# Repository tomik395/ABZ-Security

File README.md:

# ABZ Security Box

The ABZ Security Box is a security program created for ESP32-S3. This software is capable of measuring distances using a distance sensor, setting off an alarm if anything comes too close, and sending alerts via SMS. This program is specifically designed to be controlled remotely using SMS commands. The ABZ Security Box is meant to be mounted to a wall where an opening door would intersect the ultrasonic sensor line-of-sight.

This was a final team project at the University of California, San Diego for ECE 196 (Hands-on Engineering Project).

An adjustable DC Boost Converter Workshop is also attached for speaker voltage adjustments. Learn about the LM2577-ADJ IC:
For more details, see [details](ABZ%20Workshop%20LM2577-ADJ.pdf).

Please visit our website at:
https://sites.google.com/view/abz-secure

## Installation and Requirements

- You will need to install the TwilioLib library into your Arduino environment before you can compile and upload the code to your Arduino device.
- You will need a constant and stable WiFi connection to maintain SMS communication.
- This code is compatible with any ESP32 with WiFi capability. Wifi-capable Arduino devices will require code alteration due to differing WiFi connection libraries.

## PCB Design

PCB design and result images are provided on our website for users wishing to design the system from scratch, as opposed to a pre-made ESP32 device. KiCad was used to design the prototype. Since this design uses plenty of small ICs and 0402 footprint passive components, either PCB manufacturer assembly or a reflow oven is required.

If users wish to veer away from a PCB design, this code and the schematics found in the PCB files folder are compatible with any pre-made ESP32 device.

## Variables

- `commandLoopCounter` - Count of the loop iterations to control how frequently we search for new commands.
- `notificationHelp`, `notificationReset`, `notificationStatus`, `notificationLowBatt`, `notificationCritBatt`, `notificationNoBatt` - Boolean flags to track the status of notifications.
- `ssid`, `password` - Your Wifi network's SSID and password.
- `account_sid`, `auth_token`, `from_number`, `to_number` - Your Twilio account SID, Auth Token, sender number, and receiver number.
- `deactivationCode` - The deactivation code to disarm the alarm.
- `mostRecentMessage` - The most recent message sent to the Twilio phone number.
- `armed` - Boolean flag to track if the system is armed.
- `trigPin`, `echoPin`, `MosfetPin` - The pins connected to the ultrasonic sensor and alarm.
- `SOUND_SPEED`, `CM_TO_INCH`, `MAX_ANALOG_VAL`, `MAX_BATTERY_VOLTAGE` - Constants used for distance and battery level calculation.
- `duration`, `distanceInch`, `AverageDistanceInch`, `SafeDistanceInch`, `SafeDistanceInchMinus`, `SafeDistanceInchPositive`, `Safe`, `SafeCount` - Variables used for distance calculation and safety checking.
- `alpha`, `alphaDelta`, `betaDelta`, `SafeWindow`, `SafeCountTrigger` - Variables used for controlling the distance measurement and checking routines.

## SMS Commands

The following commands are available for controlling the ABZ Security System:

- `Help` - The system will reply with a list of available commands.
- `Arm` - The system will arm the alarm and start checking for intrusions.
- `Disarm` - The system will disarm the alarm.
- `Reset` - The system will ask for confirmation, then reset the device.
- `Status` - The system will send back its current status including the current battery level and whether it's armed.

  These commands are sent by replying to the system's messages.

## Key Functions

- `clearNotificationBlocks` - Clear the flags used to track if notifications have been sent.
- `status` - Get the current status of the system as a string.
- `measureAverageDistance` - Measure the average distance over a number of iterations.
- `lowBatteryNotification` - Check the battery level and send notifications if it's too low.
- `measureBattery` - Measure the current battery level.
- `measureDistance` - Measure the distance using the ultrasonic sensor once.
- `setSafeDistance` - Measure and set the safe distance.
- `questionSafety` - Check if a given distance is within the safe range.
- `setAlarmHigh` - Set the alarm to a high state (i.e., turn it on).
- `setAlarmLow` - Set the alarm to a low state (i.e., turn it off).
- `beeper` - Beep the alarm for a certain duration.
- `sendText` - Send an SMS message using Twilio.
- `getConversation` - Get the most recent message from the Twilio phone number.
- `generateMessage` - Generate a break-in alert message.
- `searchDisarmCode` - Check if the most recent message is the disarm code.
- `searchCommands` - Check if the most recent message is one of the command words.
- `alertBreakIn` - Send a break-in alert and start the alarm.
- `setup` - Set up the device. This function is called once when the device is turned on.
- `loop` - The main loop of the device. This function is called repeatedly.

## Battery Monitoring

The system includes battery level monitoring. It sends a text notification when the battery level falls below certain thresholds:

- Below 30%: A warning is sent to charge the battery
- Below 10%: A critical battery warning is sent, indicating that the system will soon shut down
- Battery level reaches 0: The system sends a final notification before shutting down

  These commands are sent by replying to the system's messages.

  The system is charged by plugging in a USB C.

## Contributing

Contributions to the ABZ Security System are welcome. Please create a pull request with your changes or enhancements, ensuring that the code is well-formatted and includes comments where necessary.

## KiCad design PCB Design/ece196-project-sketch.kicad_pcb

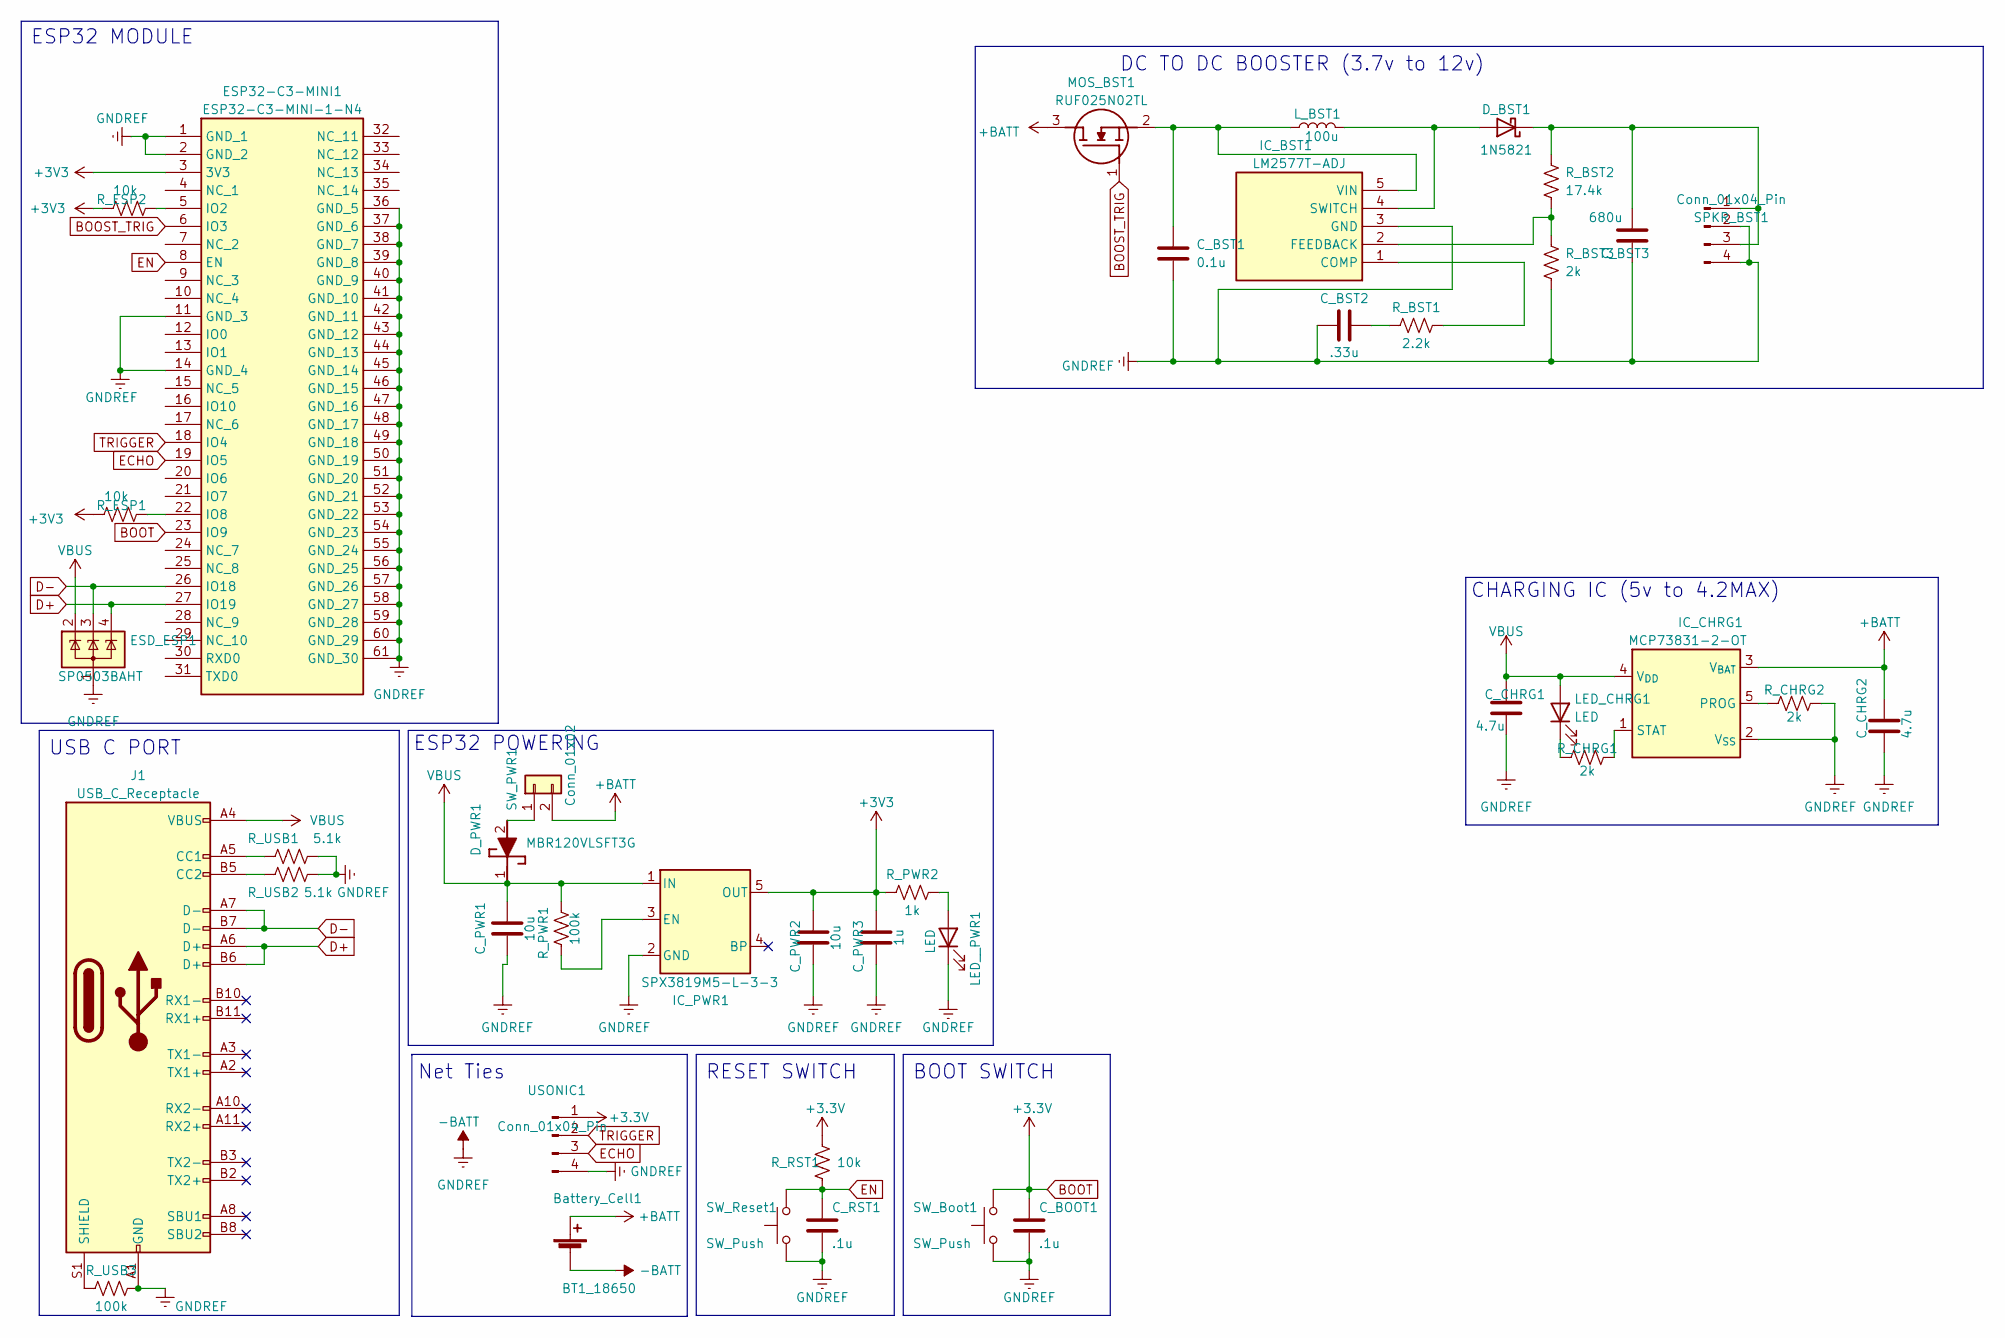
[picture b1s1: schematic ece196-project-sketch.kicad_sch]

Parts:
BT1_18650: Battery_Cell1; BatteryHolder_Keystone_1042_1x18650
C_BOOT1: .1u; C_0402_1005Metric
C_BST1: 0.1u; C_1812_4532Metric
C_BST2: .33u; C_1812_4532Metric
C_BST3: 680u; CP_Radial_D8.0mm_P5.00mm
C_CHRG1, C_CHRG2: 4.7u; C_0402_1005Metric
C_PWR1, C_PWR2: 10u; C_0402_1005Metric
C_PWR3: 1u; C_0402_1005Metric
C_RST1: .1u; C_0402_1005Metric
D_BST1: 1N5821; D_DO-201AD_P15.24mm_Horizontal
D_PWR1: MBR120VLSFT3G; SODFL3616X98N; Manufacturer_Part_Number MBR120VLSFT3G; Mouser Part Number 863-MBR120VLSFT3G
ESD_ESP1: SP0503BAHT; SOT-143
ESP32-C3-MINI1: ESP32-C3-MINI-1-N4; ESP32C3MINI1N4; Manufacturer_Part_Number ESP32-C3-MINI-1-N4; Mouser Part Number 356-ESP32-C3-MINI1N4
IC_BST1: LM2577T-ADJ; TPS75833KC; Manufacturer_Part_Number LM2577T-ADJ; Mouser Part Number 926-LM2577T-ADJ
IC_CHRG1: MCP73831-2-OT; SOT-23-5
IC_PWR1: SPX3819M5-L-3-3; SOT-23-5
J1: USB_C_Receptacle; USB_C_Receptacle_JAE_DX07S016JA1R1500
LED_CHRG1: LED; LED_0805_2012Metric
LED__PWR1: LED; LED_0805_2012Metric
L_BST1: 100u; L_Bourns-SRN1060
MOS_BST1: RUF025N02TL; Mouser Part Number 755-RUF025N02TL
R_BST1: 2.2k; R_2010_5025Metric
R_BST2: 17.4k; R_2010_5025Metric
R_BST3: 2k; R_2010_5025Metric
R_CHRG1, R_CHRG2: 2k; R_0402_1005Metric
R_ESP1, R_ESP2: 10k; R_0402_1005Metric
R_PWR1: 100k; R_0402_1005Metric
R_PWR2: 1k; R_0402_1005Metric
R_RST1: 10k; R_0402_1005Metric
R_USB1, R_USB2: 5.1k; R_0402_1005Metric
R_USB3: 100k; R_0402_1005Metric
SPKR_BST1: Conn_01x04_Pin; JST_PH_B4B-PH-K_1x04_P2.00mm_Vertical
SW_Boot1: SW_Push; SW_SPST_Omron_B3FS-100xP
SW_PWR1: Conn_01x02; PinHeader_1x02_P2.54mm_Vertical
SW_Reset1: SW_Push; SW_SPST_Omron_B3FS-100xP
USONIC1: Conn_01x04_Pin; JST_PH_B4B-PH-K_1x04_P2.00mm_Vertical

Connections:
+3V3: C_PWR2.2, C_PWR3.2, ESP32-C3-MINI1.3 (3V3), IC_PWR1.5 (OUT), R_ESP1.1, R_ESP2.1, R_PWR2.2
+BATT: BT1_18650.1 (+), C_CHRG2.2, IC_CHRG1.3 (V_{BAT}), MOS_BST1.3 (D), SW_PWR1.2
-BATT: BT1_18650.2 (-), C_BOOT1.1, C_BST1.2, C_BST2.1, C_BST3.2, C_CHRG1.1, C_CHRG2.1, C_PWR1.1, C_PWR2.1, C_PWR3.1, C_RST1.1, ESD_ESP1.1 (A), ESP32-C3-MINI1.1 (GND_1), ESP32-C3-MINI1.2 (GND_2), ESP32-C3-MINI1.11 (GND_3), ESP32-C3-MINI1.14 (GND_4), ESP32-C3-MINI1.36 (GND_5), ESP32-C3-MINI1.37 (GND_6), ESP32-C3-MINI1.38 (GND_7), ESP32-C3-MINI1.39 (GND_8), ESP32-C3-MINI1.40 (GND_9), ESP32-C3-MINI1.41 (GND_10), ESP32-C3-MINI1.42 (GND_11), ESP32-C3-MINI1.43 (GND_12), ESP32-C3-MINI1.44 (GND_13), ESP32-C3-MINI1.45 (GND_14), ESP32-C3-MINI1.46 (GND_15), ESP32-C3-MINI1.47 (GND_16), ESP32-C3-MINI1.48 (GND_17), ESP32-C3-MINI1.49 (GND_18), ESP32-C3-MINI1.50 (GND_19), ESP32-C3-MINI1.51 (GND_20), ESP32-C3-MINI1.52 (GND_21), ESP32-C3-MINI1.53 (GND_22), ESP32-C3-MINI1.54 (GND_23), ESP32-C3-MINI1.55 (GND_24), ESP32-C3-MINI1.56 (GND_25), ESP32-C3-MINI1.57 (GND_26), ESP32-C3-MINI1.58 (GND_27), ESP32-C3-MINI1.59 (GND_28), ESP32-C3-MINI1.60 (GND_29), ESP32-C3-MINI1.61 (GND_30), IC_BST1.3 (GND), IC_CHRG1.2 (V_{SS}), IC_PWR1.2 (GND), J1.A1 (GND), J1.A12 (GND), J1.B1 (GND), J1.B12 (GND), LED__PWR1.1 (K), R_BST3.2, R_CHRG2.2, R_USB1.1, R_USB2.1, R_USB3.1, SPKR_BST1.2, SPKR_BST1.4, SW_Boot1.1, SW_Reset1.1, USONIC1.4
BOOST_TRIG: ESP32-C3-MINI1.6 (IO3), MOS_BST1.1 (G)
BOOT: C_BOOT1.2, ESP32-C3-MINI1.23 (IO9), R_RST1.1, SW_Boot1.2, USONIC1.1
D+: ESD_ESP1.4 (K), ESP32-C3-MINI1.27 (IO19), J1.A6 (D+), J1.B6 (D+)
D-: ESD_ESP1.3 (K), ESP32-C3-MINI1.26 (IO18), J1.A7 (D-), J1.B7 (D-)
ECHO: ESP32-C3-MINI1.19 (IO5), USONIC1.3
EN: C_RST1.2, ESP32-C3-MINI1.8 (EN), R_RST1.2, SW_Reset1.2
unnamed: C_BST2.2, R_BST1.1
unnamed: D_BST1.2 (A), IC_BST1.4 (SWITCH), L_BST1.2
unnamed: C_BST3.1, D_BST1.1 (K), R_BST2.1, SPKR_BST1.1, SPKR_BST1.3
unnamed: D_PWR1.2 (A), SW_PWR1.1
unnamed: ESP32-C3-MINI1.5 (IO2), R_ESP2.2
unnamed: ESP32-C3-MINI1.22 (IO8), R_ESP1.2
unnamed: IC_BST1.1 (COMP), R_BST1.2
unnamed: IC_BST1.2 (FEEDBACK), R_BST2.2, R_BST3.1
unnamed: C_BST1.1, IC_BST1.5 (VIN), L_BST1.1, MOS_BST1.2 (S)
unnamed: IC_CHRG1.5 (PROG), R_CHRG2.1
unnamed 19: IC_CHRG1.1 (STAT), R_CHRG1.2; also elsewhere on the board
unnamed: IC_PWR1.3 (EN), R_PWR1.1
unnamed: J1.A5 (CC1), R_USB1.2
unnamed: J1.B5 (CC2), R_USB2.2
unnamed: J1.S1 (SHIELD), R_USB3.2
unnamed: LED_CHRG1.1 (K), R_CHRG1.1
unnamed: LED__PWR1.2 (A), R_PWR2.1
TRIGGER: ESP32-C3-MINI1.18 (IO4), USONIC1.2
VBUS: C_CHRG1.2, C_PWR1.2, D_PWR1.1 (K), ESD_ESP1.2 (K), IC_CHRG1.4 (V_{DD}), IC_PWR1.1 (IN), J1.A4 (VBUS), J1.A9 (VBUS), J1.B4 (VBUS), J1.B9 (VBUS), LED_CHRG1.2 (A), R_PWR1.2; also elsewhere on the board

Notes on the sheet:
USB C PORT
BOOT SWITCH
Net Ties
ESP32 POWERING
CHARGING IC (5v to 4.2MAX)
RESET SWITCH
DC TO DC BOOSTER (3.7v to 12v)
ESP32 MODULE

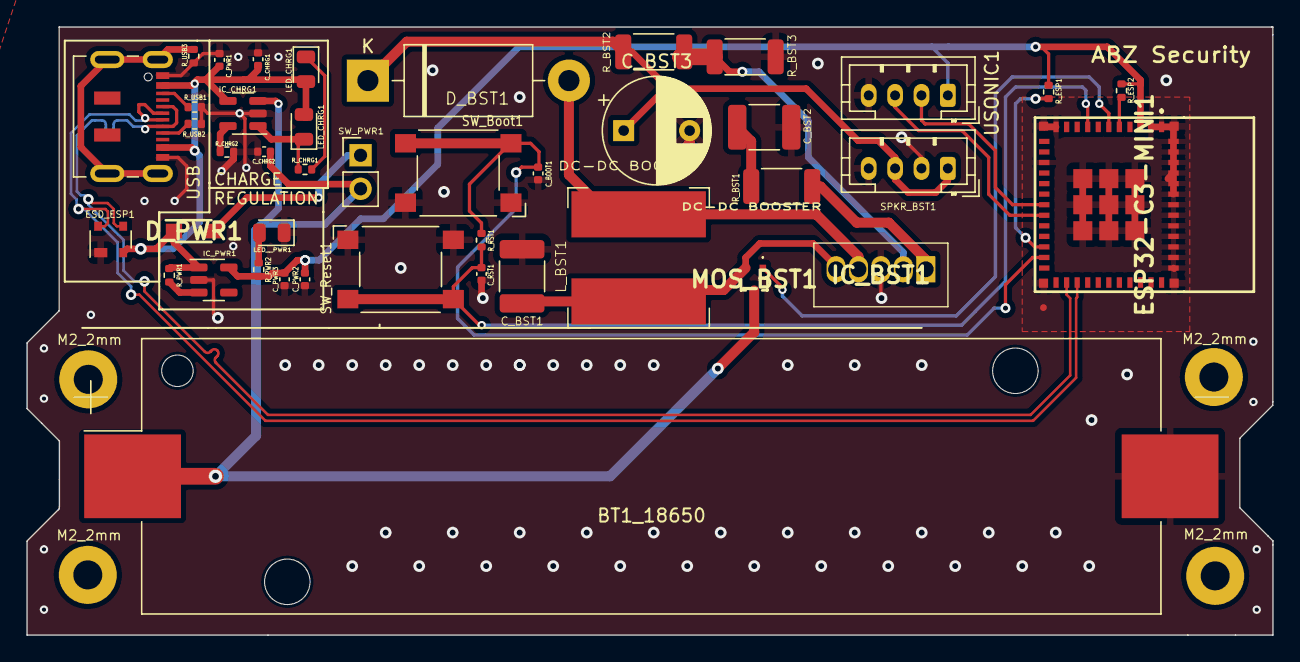
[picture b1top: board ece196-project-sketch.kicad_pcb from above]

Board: 2 copper layers, 94.5 x 46.1 mm, 46 parts (0 on the bottom side), 28 nets.

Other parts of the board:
LED_CHRG1#2: LED; LED_0805_2012Metric
M2_2mm, M2_2mm#2, M2_2mm#3, M2_2mm#4: MountingHole_2.2mm_M2_Pad

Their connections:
unnamed 19: LED_CHRG1#2.1 (K); also elsewhere on the board
VBUS: LED_CHRG1#2.2 (A); also elsewhere on the board

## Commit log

2023-07-14 Uploaded LM2577T-ADJ Workshop
    Learn how to adjust the voltage fed to your speaker
2023-07-14 Added PCB Files
